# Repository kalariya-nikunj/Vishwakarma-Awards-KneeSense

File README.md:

# KneeSense — Vishwakarma Awards Prototype

KneeSense is an experimental knee-motion sensing project being prepared for the Vishwakarma Awards. The current development workflow uses two sensor nodes, identified by the test logger as `KS_THIGH` and `KS_SHANK`, to collect accelerometer and gyroscope readings over Bluetooth Low Energy (BLE). Python is used to record readings and generate signal plots.

## Prototype status

This repository contains sensor firmware, a Python BLE logger, three CSV recordings with matching PNG graphs, SolidWorks models, and a KiCad project with custom libraries, fabrication exports, and historical backups. A finished report and documented reference-measurement evaluation are still pending.

The supplied files were copied from the local project folder with their original filenames and contents preserved. Recordings and graphs demonstrate the available acquisition artifacts; they do not establish measurement accuracy or clinical performance. Firmware compilation, CAD assembly resolution, and PCB manufacturability have not been verified during this import.

Knee-angle estimation, sensor alignment/calibration, synchronization between nodes, and comparison against a reference measurement remain to be documented and evaluated. No validated knee-angle accuracy, osteoarthritis (OA) detection, diagnosis, or treatment performance is claimed. Signal plots alone do not establish these capabilities.

## Repository layout

| Path | Intended contents |
| --- | --- |
| `firmware/` | Sensor-node source, board details, build/flash instructions |
| `software/` | Python BLE logger |
| `data/raw/` | Original recordings, preserved without manual edits |
| `results/graphs/` | Derived plots linked to source recordings |
| `hardware/KiCad/` | Schematics, PCB layouts, libraries, fabrication exports |
| `mechanical/CAD/` | Editable models and exported mechanical parts |
| `media/photos/` | Link to externally hosted prototype photos |
| `media/videos/` | Link to externally hosted demonstrations and recordings |
| `docs/report/` | Brief project report and supporting notes |

## Project files and demonstration media

- [Sensor firmware](firmware/Firmware_thigh_shank/Firmware_thigh_shank.ino): set `DEVICE_NAME` to `KS_THIGH` for one board and `KS_SHANK` for the other. The source includes ArduinoBLE and LSM6DS3 libraries, a target 50 Hz sampling interval, and stationary gyroscope bias calibration at startup. Board package and tested library versions still need recording.
- [Python BLE logger](software/kneesense_ble_logger.py): receives acceleration and angular velocity from both nodes, writes CSV, and plots four signal panels. It does not calculate knee angle or classify OA.
- [Raw recordings](data/raw/) and [matching graphs](results/graphs/): match files by their unchanged `kneesense_YYYYMMDD_HHMMSS` basename. Run conditions and participant/movement details remain to be documented.
- [KiCad project](hardware/KiCad/Prototype_KneeSense_V1/): preserves the supplied project tree and relative library/model references. See [hardware import notes](hardware/KiCad/README.md) before using fabrication files.
- [SolidWorks models](mechanical/CAD/3D-Models/): `Assem2.SLDASM`, `bottom plate_V5.SLDPRT`, and `casing_V4.SLDPRT`; assembly references have not been opened/verified.
- [Photos and videos on Google Drive](https://drive.google.com/drive/folders/1JCOzSr-7obGCgrjGczuZRWfTyBF06cKV?usp=sharing): supplied by the project owner and hosted externally to avoid storing large media in Git history. Folder contents and viewer access were not verified during import. Check access in a signed-out browser before sharing with judges. No Drive permissions were changed.

The original `Untitled-1.txt` file remains in `media/videos/`. The Drive folder is the intended location for demonstration media.

## Python setup

`requirements.txt` lists the logger's external dependencies. Use Python 3.10 or newer for the syntax used in the supplied script. Package versions are intentionally unpinned until the tested acquisition environment is recorded.

```powershell
python -m venv .venv
.\.venv\Scripts\Activate.ps1
python -m pip install -r requirements.txt
python software/kneesense_ble_logger.py
```

Run from the repository root with both correctly configured sensor nodes nearby and Bluetooth enabled. The unchanged logger records for 60 seconds and saves new CSV/PNG files to `kneesense_output/` relative to the working directory. After recording, copy CSVs to `data/raw/` and PNGs to `results/graphs/`, preserving filenames and documenting the session. The logger is not executed automatically by this repository.

## Adding evidence

1. Record board, sensor, firmware, and tested software versions for the supplied source.
2. Preserve original filenames and raw data; use a session record to link recordings, plots, and videos.
3. Complete [the data dictionary](docs/DATA_DICTIONARY.md) against the actual firmware and logger.
4. Follow [the recording instructions](docs/RECORDING_INSTRUCTIONS.md) and copy [the session template](docs/SESSION_TEMPLATE.md) for each run.
5. Write the brief report using [the report outline](docs/report/REPORT_TEMPLATE.md), separating observed behavior from planned work.

Only include material suitable for sharing. Record participant codes rather than personal identifiers in session notes; confirm permission before adding identifiable participant media.

Keep original recordings and design revisions available when adding or updating evidence.

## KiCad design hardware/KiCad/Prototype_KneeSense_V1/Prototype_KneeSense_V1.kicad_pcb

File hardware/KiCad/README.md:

# Supplied hardware project

`Prototype_KneeSense_V1/` contains the supplied KiCad project tree, copied with original names and contents. Open `Prototype_KneeSense_V1.kicad_pro` in that directory. Keep `fp-lib-table`, `libraries/`, and `3dmodels/` together; the inspected custom footprint and model paths use `${KIPRJMOD}`.

Multiple Gerber ZIP variants, an extracted `gerbers/` directory, historical backup ZIPs, and a nested `kicad project/` are preserved. Their presence does not identify which revision was fabricated or approved. Confirm the intended board/export revision before ordering fabrication; no design-rule or manufacturing checks were performed during import.

The bundled Adafruit reference folder includes its original `license.txt` and `README.md`. Its `Adafruit SDIO microSD.sch` is only 7 bytes and contains `<?xml`, so it appears incomplete. It is preserved as supplied and must not be relied on as a complete reference schematic. This is separate from the main `Prototype_KneeSense_V1.kicad_sch` file.

KiCad local preference files (`.kicad_prl`) and historical backups are included to preserve the supplied collection. The working prototype's relationship to each archived design still needs documentation.

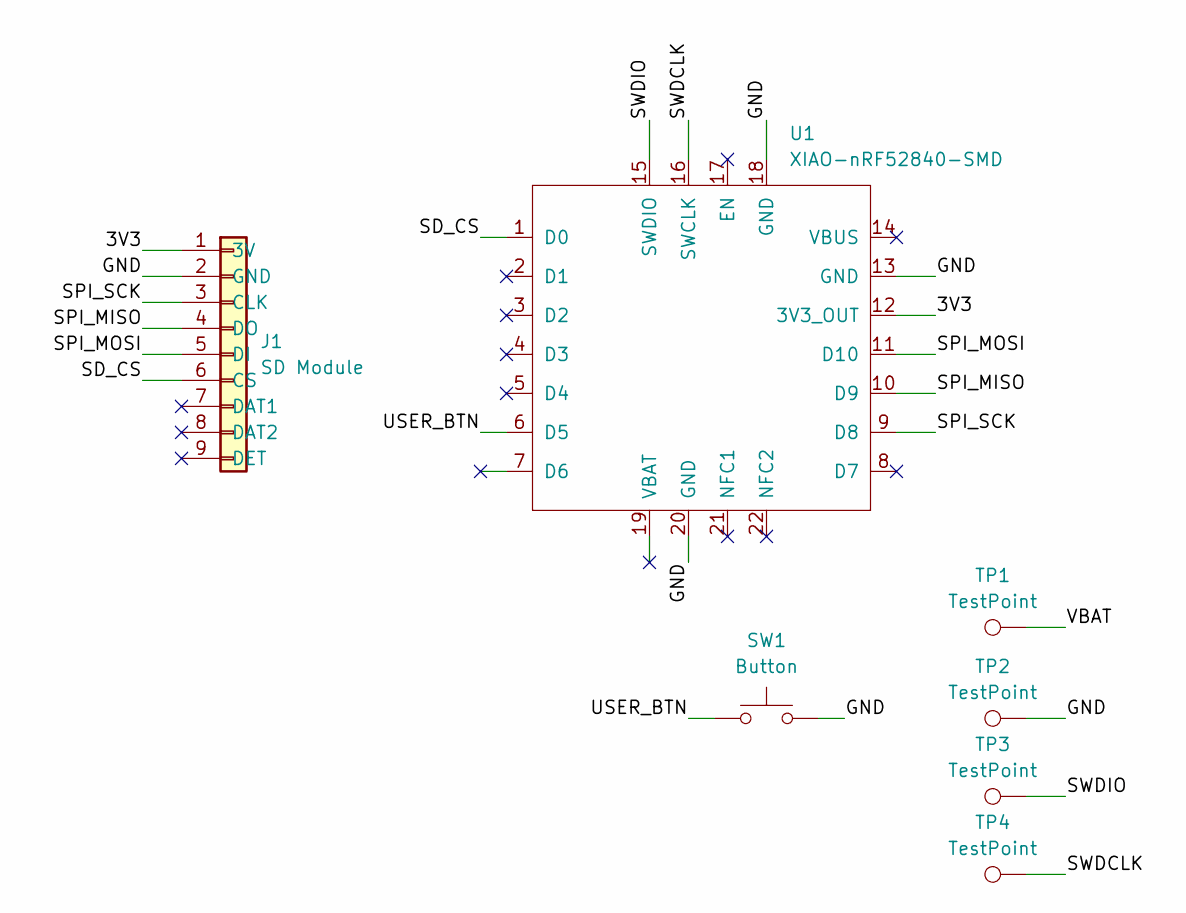
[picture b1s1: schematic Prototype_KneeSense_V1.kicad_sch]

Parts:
J1: SD Module; microSD_4682
SW1: Button; SW_SPST_PTS645Sx43SMTR92
TP1, TP2, TP3, TP4: TestPoint; TestPoint_Pad_4.0x4.0mm
U1: XIAO-nRF52840-SMD

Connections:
/3V3: J1.1 (3V), U1.12 (3V3_OUT)
/GND: J1.2 (GND), SW1.2 (GND), TP2.1 (1_1), U1.13 (GND), U1.18 (GND), U1.20 (GND)
/SD_CS: J1.6 (CS), U1.1 (D0)
/SPI_MISO: J1.4 (DO), U1.10 (D9)
/SPI_MOSI: J1.5 (DI), U1.11 (D10)
/SPI_SCK: J1.3 (CLK), U1.9 (D8)
/SWDCLK: TP4.1 (1_1), U1.16 (SWCLK)
/SWDIO: TP3.1 (1_1), U1.15 (SWDIO)
/USER_BTN: SW1.1 (USER_BTN), U1.6 (D5)
/VBAT: TP1.1 (1_1)

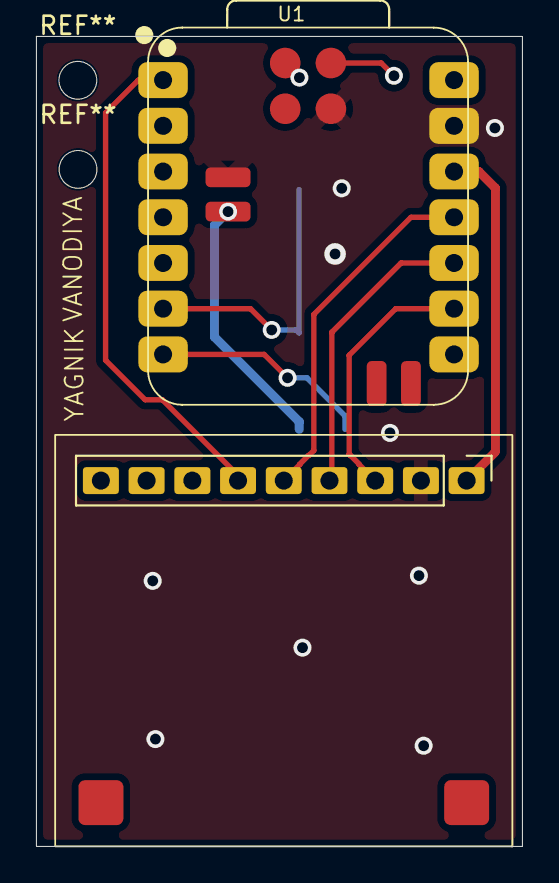
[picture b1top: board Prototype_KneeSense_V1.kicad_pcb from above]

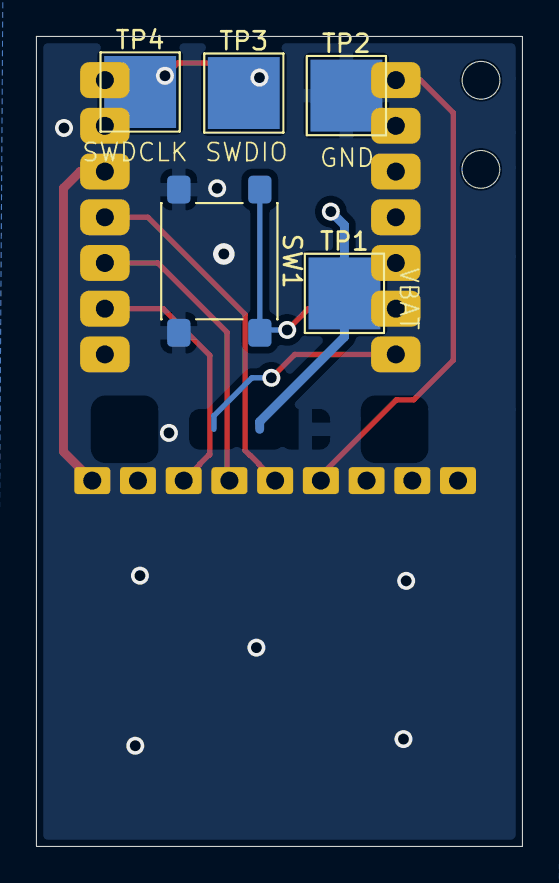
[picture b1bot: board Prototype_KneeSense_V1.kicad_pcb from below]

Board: 2 copper layers, 27.0 x 45.0 mm, 7 parts (5 on the bottom side), 9 nets.
